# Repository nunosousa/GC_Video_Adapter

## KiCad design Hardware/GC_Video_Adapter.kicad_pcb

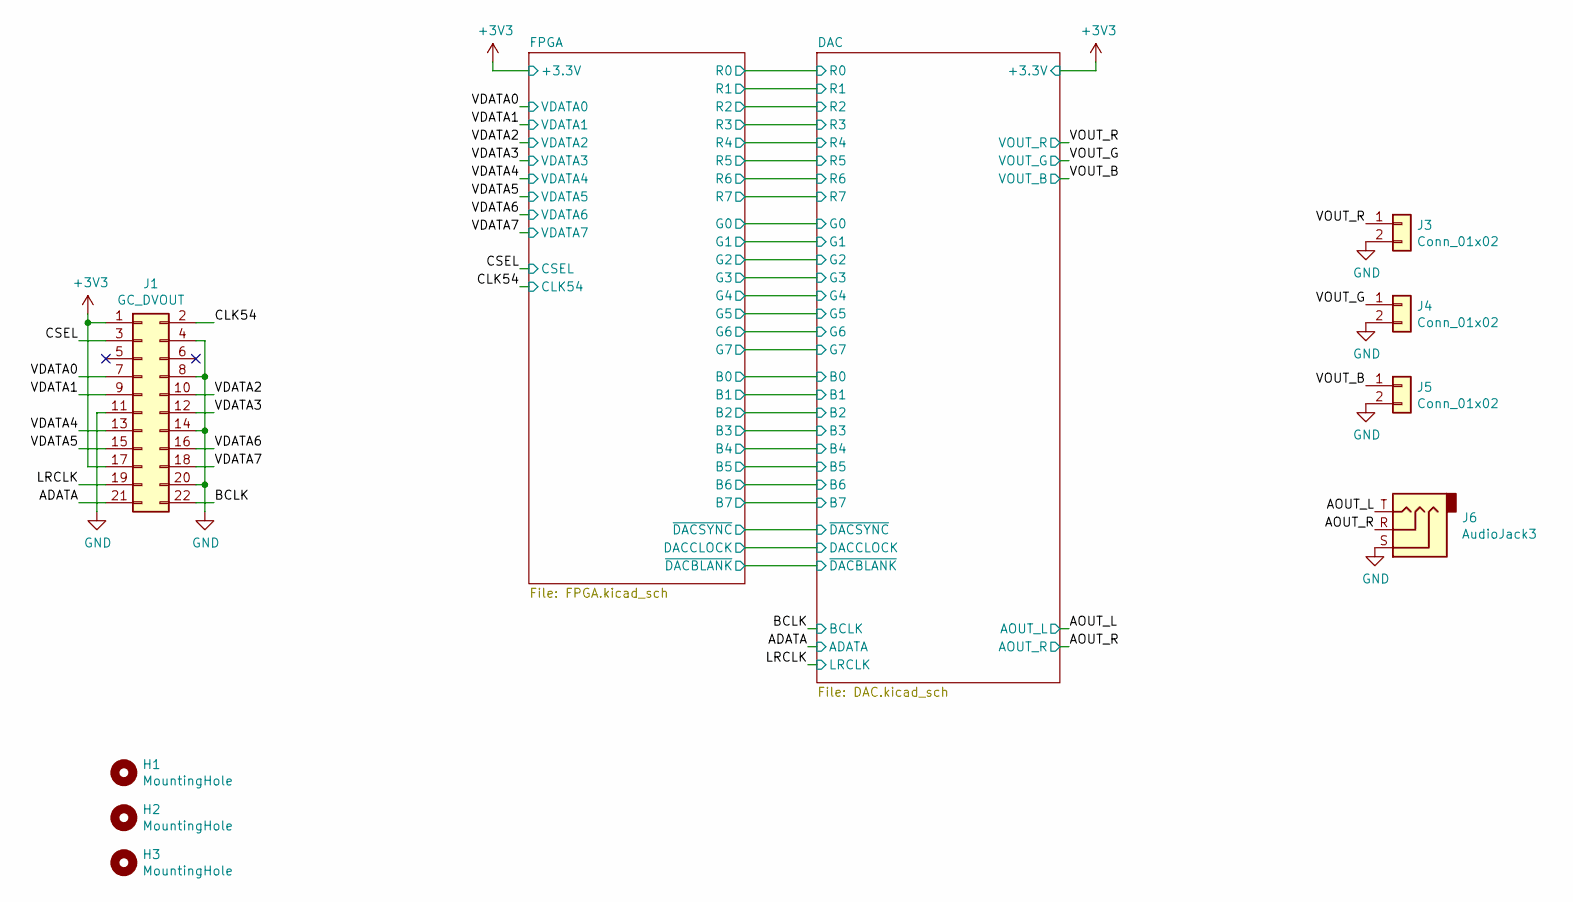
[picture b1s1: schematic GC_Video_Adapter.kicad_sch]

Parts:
H1, H2, H3: MountingHole; MountingHole_3.2mm_M3
J1: GC_DVOUT; GC-Connector-01; Manufacturer Part Number GC-Connector-01
J3, J4, J5: Conn_01x02; SolderWire-0.5sqmm_1x02_P4.6mm_D0.9mm_OD2.1mm
J6: AudioJack3; Jack_3.5mm_CUI_SJ1-3533NG_Horizontal; Manufacturer Part Number SJ1-3533NG

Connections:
+3V3: J1.1, J1.17; also elsewhere on the board
/ADATA: J1.21; also elsewhere on the board
/AOUT_L: J6.T; also elsewhere on the board
/AOUT_R: J6.R; also elsewhere on the board
/BCLK: J1.22; also elsewhere on the board
/CLK54: J1.2; also elsewhere on the board
/CSEL: J1.3; also elsewhere on the board
/LRCLK: J1.19; also elsewhere on the board
/VDATA0: J1.7; also elsewhere on the board
/VDATA1: J1.9; also elsewhere on the board
/VDATA2: J1.10; also elsewhere on the board
/VDATA3: J1.12; also elsewhere on the board
/VDATA4: J1.13; also elsewhere on the board
/VDATA5: J1.15; also elsewhere on the board
/VDATA6: J1.16; also elsewhere on the board
/VDATA7: J1.18; also elsewhere on the board
/VOUT_B: J5.1; also elsewhere on the board
/VOUT_G: J4.1; also elsewhere on the board
/VOUT_R: J3.1; also elsewhere on the board
GND: J1.4, J1.8, J1.11, J1.14, J1.20, J3.2, J4.2, J5.2, J6.S; also elsewhere on the board

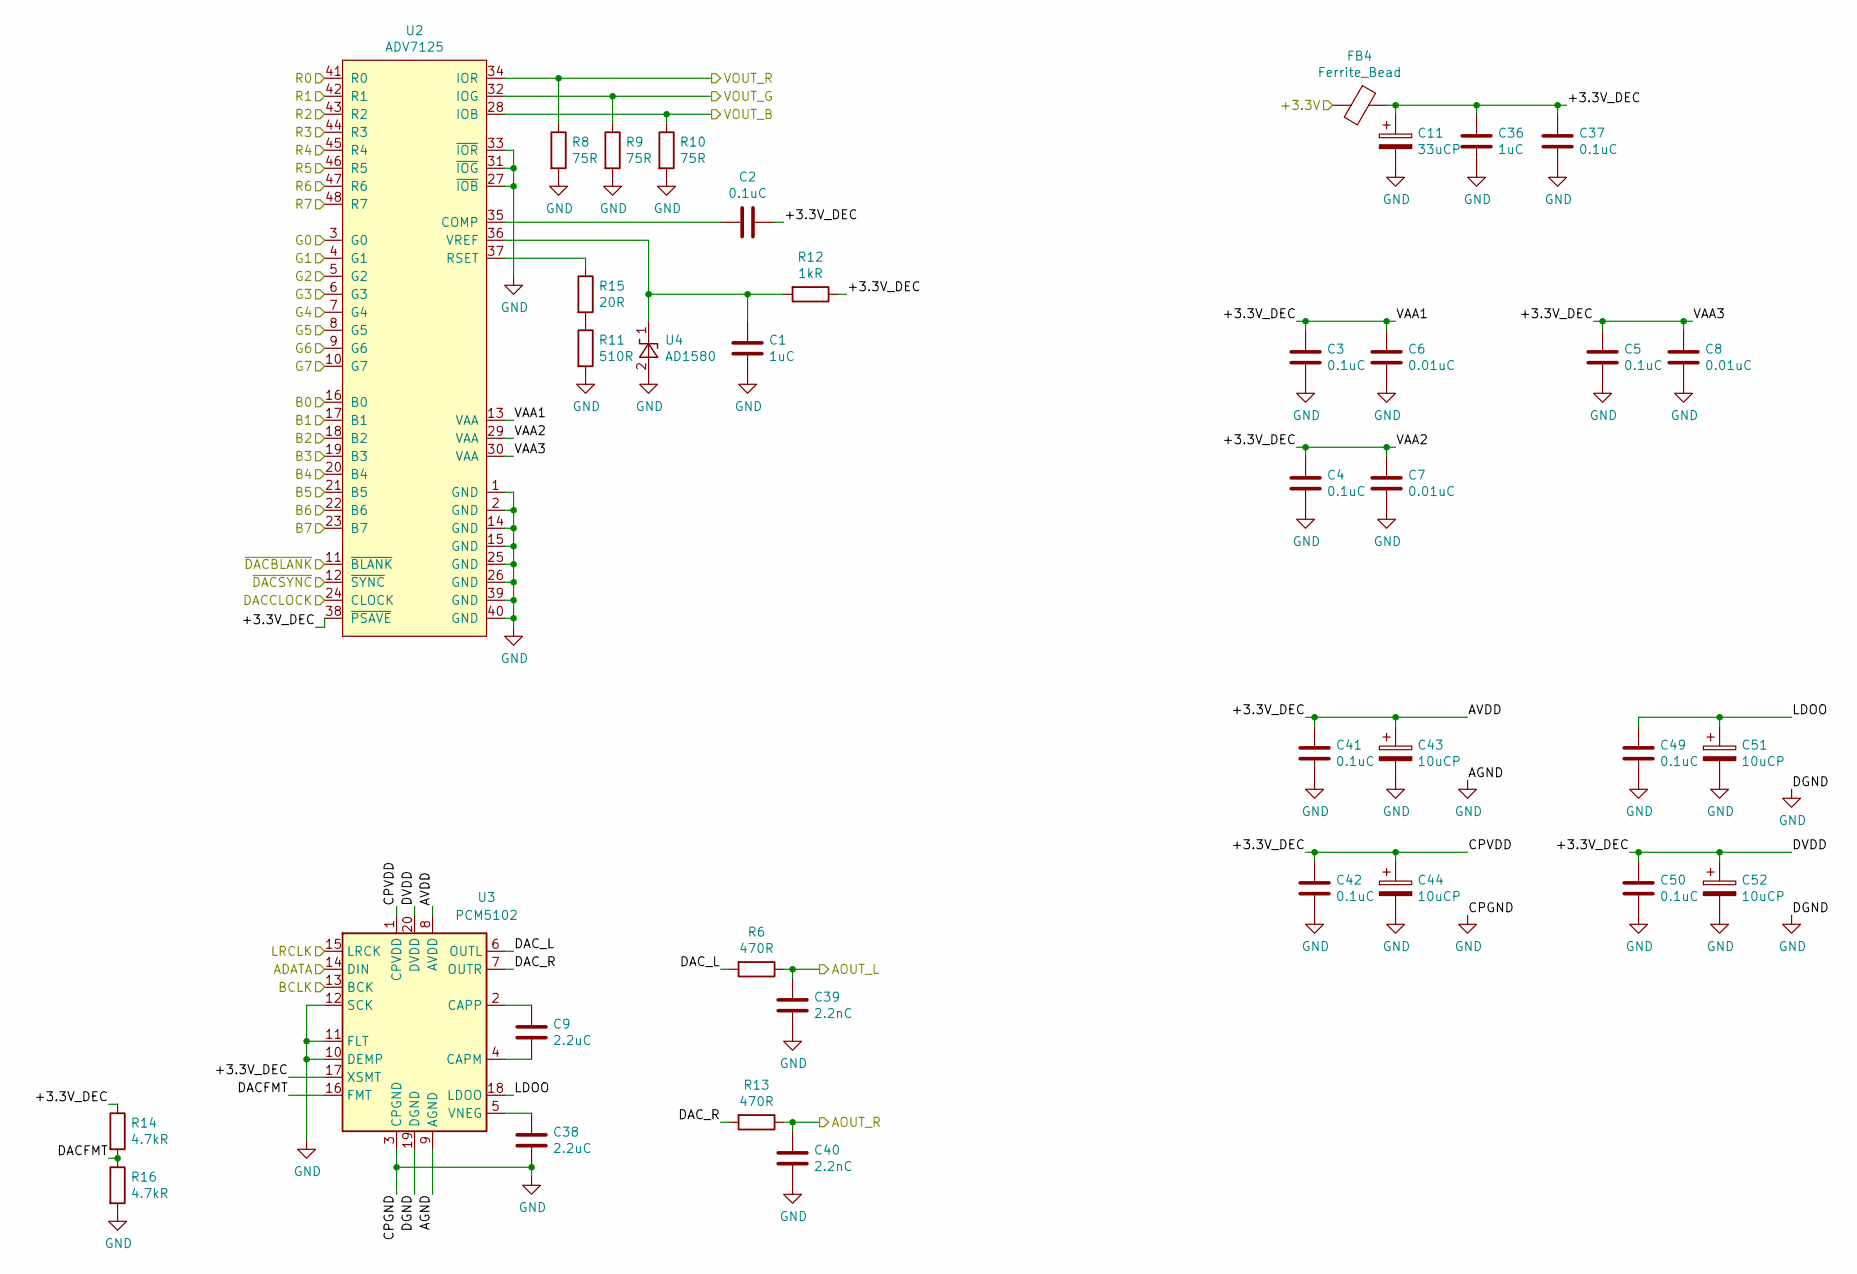
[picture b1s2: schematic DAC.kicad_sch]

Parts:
C1, C36: 1uC; C_0805_2012Metric_Pad1.18x1.45mm_HandSolder; Manufacturer Part Number CC0805MKX7R7BB105
C2, C3, C4, C5, C37, C41, C42, C49, C50: 0.1uC; C_0805_2012Metric_Pad1.18x1.45mm_HandSolder; Manufacturer Part Number AC0805KRX7R7BB104
C6, C7, C8: 0.01uC; C_0805_2012Metric_Pad1.18x1.45mm_HandSolder; Manufacturer Part Number CC0805KRX7R9BB103
C9, C38: 2.2uC; C_0805_2012Metric_Pad1.18x1.45mm_HandSolder; Manufacturer Part Number TMK212B7225KG-TR
C11: 33uCP; CP_EIA-3528-21_Kemet-B_Pad1.50x2.35mm_HandSolder; Manufacturer Part Number TAJB336K006RNJ
C39, C40: 2.2nC; C_0805_2012Metric_Pad1.18x1.45mm_HandSolder; Manufacturer Part Number FCP0805H222J-J1
C43, C44, C51, C52: 10uCP; CP_EIA-3216-18_Kemet-A_Pad1.58x1.35mm_HandSolder; Manufacturer Part Number TAJA106K006SNJ
FB4: Ferrite_Bead; L_0805_2012Metric_Pad1.15x1.40mm_HandSolder; Manufacturer Part Number BLM21SP471SH1D
R6, R13: 470R; R_0805_2012Metric_Pad1.20x1.40mm_HandSolder; Manufacturer Part Number CRCW0805470RJNEA
R8, R9, R10: 75R; R_0805_2012Metric_Pad1.20x1.40mm_HandSolder; Manufacturer Part Number RC0805FR-0775RL
R11: 510R; R_0805_2012Metric_Pad1.20x1.40mm_HandSolder; Manufacturer Part Number RT0805BRD07510RL
R12: 1kR; R_0805_2012Metric_Pad1.20x1.40mm_HandSolder; Manufacturer Part Number RC0805FR-071KL
R14, R16: 4.7kR; R_0805_2012Metric_Pad1.20x1.40mm_HandSolder; Manufacturer Part Number RC0805FR-074K7L
R15: 20R; R_0805_2012Metric_Pad1.20x1.40mm_HandSolder; Manufacturer Part Number RT0805BRD0720RL
U2: ADV7125; LQFP-48_7x7mm_P0.5mm; Manufacturer Part Number ADV7125KSTZ50-REEL
U3: PCM5102; TSSOP-20_4.4x6.5mm_P0.65mm; Manufacturer Part Number PCM5102APWR
U4: AD1580; SOT-23; Manufacturer Part Number AD1580BRTZ-REEL7

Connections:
+3V3: FB4.2; also elsewhere on the board
/ADATA: U3.14 (DIN); also elsewhere on the board
/AOUT_L: C39.1, R6.1; also elsewhere on the board
/AOUT_R: C40.1, R13.1; also elsewhere on the board
/BCLK: U3.13 (BCK); also elsewhere on the board
/DAC/+3.3V_DEC: C2.1, C3.1, C4.1, C5.1, C6.1, C7.1, C8.1, C11.1, C36.1, C37.1, C41.1, C42.1, C43.1, C44.1, C50.1, C52.1, FB4.1, R12.1, R14.1, U2.13 (VAA), U2.29 (VAA), U2.30 (VAA), U2.38 (~PSAVE), U3.1 (CPVDD), U3.8 (AVDD), U3.17 (XSMT), U3.20 (DVDD)
/DAC/B0: U2.16 (B0); also elsewhere on the board
/DAC/B1: U2.17 (B1); also elsewhere on the board
/DAC/B2: U2.18 (B2); also elsewhere on the board
/DAC/B3: U2.19 (B3); also elsewhere on the board
/DAC/B4: U2.20 (B4); also elsewhere on the board
/DAC/B5: U2.21 (B5); also elsewhere on the board
/DAC/B6: U2.22 (B6); also elsewhere on the board
/DAC/B7: U2.23 (B7); also elsewhere on the board
/DAC/DACCLOCK: U2.24 (CLOCK); also elsewhere on the board
/DAC/DACFMT: R14.2, R16.1, U3.16 (FMT)
/DAC/DAC_L: R6.2, U3.6 (OUTL)
/DAC/DAC_R: R13.2, U3.7 (OUTR)
/DAC/G0: U2.3 (G0); also elsewhere on the board
/DAC/G1: U2.4 (G1); also elsewhere on the board
/DAC/G2: U2.5 (G2); also elsewhere on the board
/DAC/G3: U2.6 (G3); also elsewhere on the board
/DAC/G4: U2.7 (G4); also elsewhere on the board
/DAC/G5: U2.8 (G5); also elsewhere on the board
/DAC/G6: U2.9 (G6); also elsewhere on the board
/DAC/G7: U2.10 (G7); also elsewhere on the board
/DAC/LDOO: C49.1, C51.1, U3.18 (LDOO)
/DAC/R0: U2.41 (R0); also elsewhere on the board
/DAC/R1: U2.42 (R1); also elsewhere on the board
/DAC/R2: U2.43 (R2); also elsewhere on the board
/DAC/R3: U2.44 (R3); also elsewhere on the board
/DAC/R4: U2.45 (R4); also elsewhere on the board
/DAC/R5: U2.46 (R5); also elsewhere on the board
/DAC/R6: U2.47 (R6); also elsewhere on the board
/DAC/R7: U2.48 (R7); also elsewhere on the board
/DAC/~DACBLANK: U2.11 (~BLANK); also elsewhere on the board
/DAC/~DACSYNC: U2.12 (~SYNC); also elsewhere on the board
/LRCLK: U3.15 (LRCK); also elsewhere on the board
/VOUT_B: R10.1, U2.28 (IOB); also elsewhere on the board
/VOUT_G: R9.1, U2.32 (IOG); also elsewhere on the board
/VOUT_R: R8.1, U2.34 (IOR); also elsewhere on the board
GND: C1.2, C3.2, C4.2, C5.2, C6.2, C7.2, C8.2, C11.2, C36.2, C37.2, C38.2, C39.2, C40.2, C41.2, C42.2, C43.2, C44.2, C49.2, C50.2, C51.2, C52.2, R8.2, R9.2, R10.2, R11.2, R16.2, U2.1 (GND), U2.2 (GND), U2.14 (GND), U2.15 (GND), U2.25 (GND), U2.26 (GND), U2.27 (~IOB), U2.31 (~IOG), U2.33 (~IOR), U2.39 (GND), U2.40 (GND), U3.3 (CPGND), U3.9 (AGND), U3.10 (DEMP), U3.11 (FLT), U3.12 (SCK), U3.19 (DGND), U4.2 (A); also elsewhere on the board
unnamed: C1.1, R12.2, U2.36 (VREF), U4.1 (K)
unnamed: C2.2, U2.35 (COMP)
unnamed: C9.1, U3.2 (CAPP)
unnamed: C9.2, U3.4 (CAPM)
unnamed: C38.1, U3.5 (VNEG)
unnamed: R11.1, R15.2
unnamed: R15.1, U2.37 (RSET)

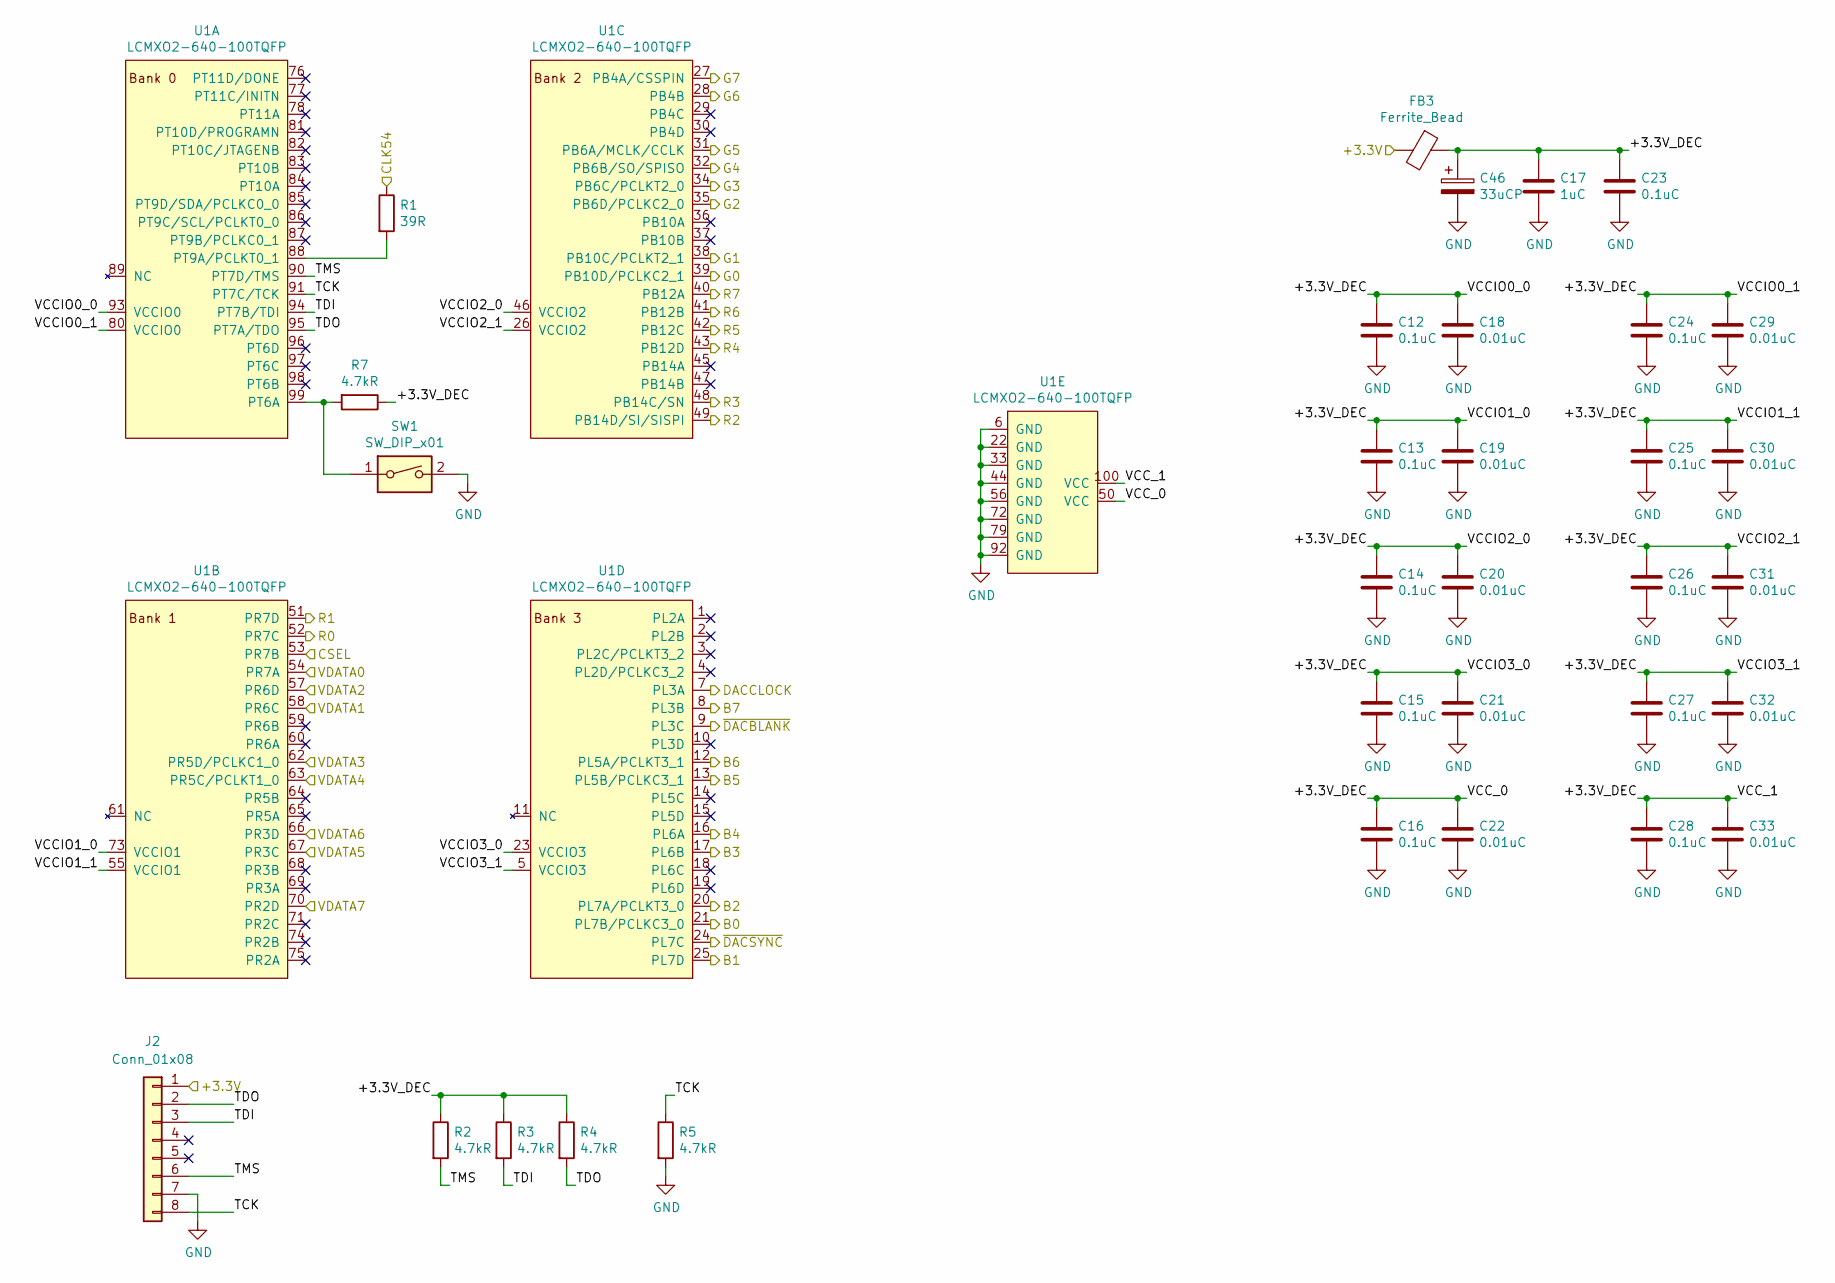
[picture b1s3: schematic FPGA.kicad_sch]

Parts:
C12, C13, C14, C15, C16, C23, C24, C25, C26, C27, C28: 0.1uC; C_0805_2012Metric_Pad1.18x1.45mm_HandSolder; Manufacturer Part Number AC0805KRX7R7BB104
C17: 1uC; C_0805_2012Metric_Pad1.18x1.45mm_HandSolder; Manufacturer Part Number CC0805MKX7R7BB105
C18, C19, C20, C21, C22, C29, C30, C31, C32, C33: 0.01uC; C_0805_2012Metric_Pad1.18x1.45mm_HandSolder; Manufacturer Part Number CC0805KRX7R9BB103
C46: 33uCP; CP_EIA-3528-21_Kemet-B_Pad1.50x2.35mm_HandSolder; Manufacturer Part Number TAJB336K006RNJ
FB3: Ferrite_Bead; L_0805_2012Metric_Pad1.15x1.40mm_HandSolder; Manufacturer Part Number BLM21SP471SH1D
J2: Conn_01x08; PinHeader_1x08_P2.54mm_Vertical; Manufacturer Part Number 0022284081
R1: 39R; R_0805_2012Metric_Pad1.20x1.40mm_HandSolder; Manufacturer Part Number RC0805FR-0739RL
R2, R3, R4, R5, R7: 4.7kR; R_0805_2012Metric_Pad1.20x1.40mm_HandSolder; Manufacturer Part Number RC0805FR-074K7L
SW1: SW_DIP_x01; SW_DIP_SPSTx01_Slide_6.7x4.1mm_W7.62mm_P2.54mm_LowProfile; Manufacturer Part Number DS04-254-2L-01BK
U1: LCMXO2-640-100TQFP; TQFP-100_14x14mm_P0.5mm; Manufacturer Part Number LCMXO2-640HC-4TG100I

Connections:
+3V3: FB3.2, J2.1; also elsewhere on the board
/CLK54: R1.1; also elsewhere on the board
/CSEL: U1.53 (PR7B); also elsewhere on the board
/DAC/B0: U1.21 (PL7B/PCLKC3_0); also elsewhere on the board
/DAC/B1: U1.25 (PL7D); also elsewhere on the board
/DAC/B2: U1.20 (PL7A/PCLKT3_0); also elsewhere on the board
/DAC/B3: U1.17 (PL6B); also elsewhere on the board
/DAC/B4: U1.16 (PL6A); also elsewhere on the board
/DAC/B5: U1.13 (PL5B/PCLKC3_1); also elsewhere on the board
/DAC/B6: U1.12 (PL5A/PCLKT3_1); also elsewhere on the board
/DAC/B7: U1.8 (PL3B); also elsewhere on the board
/DAC/DACCLOCK: U1.7 (PL3A); also elsewhere on the board
/DAC/G0: U1.39 (PB10D/PCLKC2_1); also elsewhere on the board
/DAC/G1: U1.38 (PB10C/PCLKT2_1); also elsewhere on the board
/DAC/G2: U1.35 (PB6D/PCLKC2_0); also elsewhere on the board
/DAC/G3: U1.34 (PB6C/PCLKT2_0); also elsewhere on the board
/DAC/G4: U1.32 (PB6B/SO/SPISO); also elsewhere on the board
/DAC/G5: U1.31 (PB6A/MCLK/CCLK); also elsewhere on the board
/DAC/G6: U1.28 (PB4B); also elsewhere on the board
/DAC/G7: U1.27 (PB4A/CSSPIN); also elsewhere on the board
/DAC/R0: U1.52 (PR7C); also elsewhere on the board
/DAC/R1: U1.51 (PR7D); also elsewhere on the board
/DAC/R2: U1.49 (PB14D/SI/SISPI); also elsewhere on the board
/DAC/R3: U1.48 (PB14C/SN); also elsewhere on the board
/DAC/R4: U1.43 (PB12D); also elsewhere on the board
/DAC/R5: U1.42 (PB12C); also elsewhere on the board
/DAC/R6: U1.41 (PB12B); also elsewhere on the board
/DAC/R7: U1.40 (PB12A); also elsewhere on the board
/DAC/~DACBLANK: U1.9 (PL3C); also elsewhere on the board
/DAC/~DACSYNC: U1.24 (PL7C); also elsewhere on the board
/FPGA/+3.3V_DEC: C12.1, C13.1, C14.1, C15.1, C16.1, C17.1, C18.1, C19.1, C20.1, C21.1, C22.1, C23.1, C24.1, C25.1, C26.1, C27.1, C28.1, C29.1, C30.1, C31.1, C32.1, C33.1, C46.1, FB3.1, R2.1, R3.1, R4.1, R7.1, U1.5 (VCCIO3), U1.23 (VCCIO3), U1.26 (VCCIO2), U1.46 (VCCIO2), U1.50 (VCC), U1.55 (VCCIO1), U1.73 (VCCIO1), U1.80 (VCCIO0), U1.93 (VCCIO0), U1.100 (VCC)
/FPGA/TCK: J2.8, R5.1, U1.91 (PT7C/TCK)
/FPGA/TDI: J2.3, R3.2, U1.94 (PT7B/TDI)
/FPGA/TDO: J2.2, R4.2, U1.95 (PT7A/TDO)
/FPGA/TMS: J2.6, R2.2, U1.90 (PT7D/TMS)
/VDATA0: U1.54 (PR7A); also elsewhere on the board
/VDATA1: U1.58 (PR6C); also elsewhere on the board
/VDATA2: U1.57 (PR6D); also elsewhere on the board
/VDATA3: U1.62 (PR5D/PCLKC1_0); also elsewhere on the board
/VDATA4: U1.63 (PR5C/PCLKT1_0); also elsewhere on the board
/VDATA5: U1.67 (PR3C); also elsewhere on the board
/VDATA6: U1.66 (PR3D); also elsewhere on the board
/VDATA7: U1.70 (PR2D); also elsewhere on the board
GND: C12.2, C13.2, C14.2, C15.2, C16.2, C17.2, C18.2, C19.2, C20.2, C21.2, C22.2, C23.2, C24.2, C25.2, C26.2, C27.2, C28.2, C29.2, C30.2, C31.2, C32.2, C33.2, C46.2, J2.7, R5.2, SW1.2, U1.6 (GND), U1.22 (GND), U1.33 (GND), U1.44 (GND), U1.56 (GND), U1.72 (GND), U1.79 (GND), U1.92 (GND); also elsewhere on the board
unnamed: R1.2, U1.88 (PT9A/PCLKT0_1)
unnamed: R7.2, SW1.1, U1.99 (PT6A)

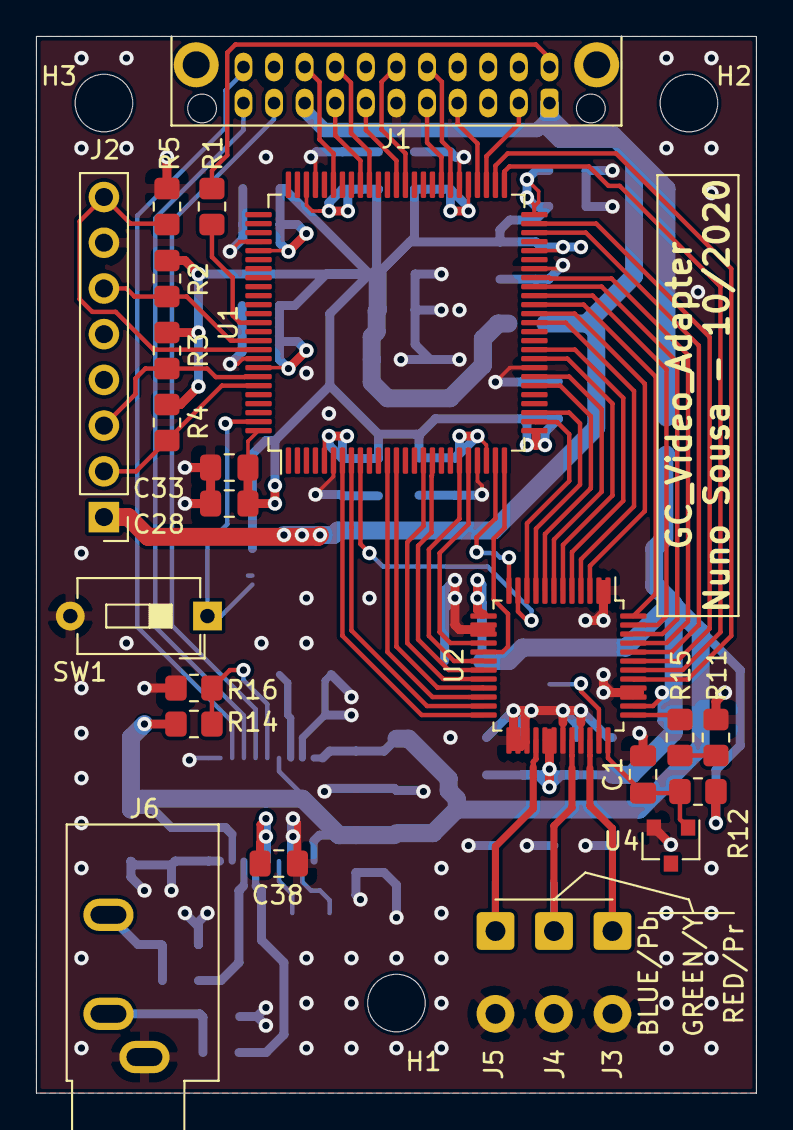
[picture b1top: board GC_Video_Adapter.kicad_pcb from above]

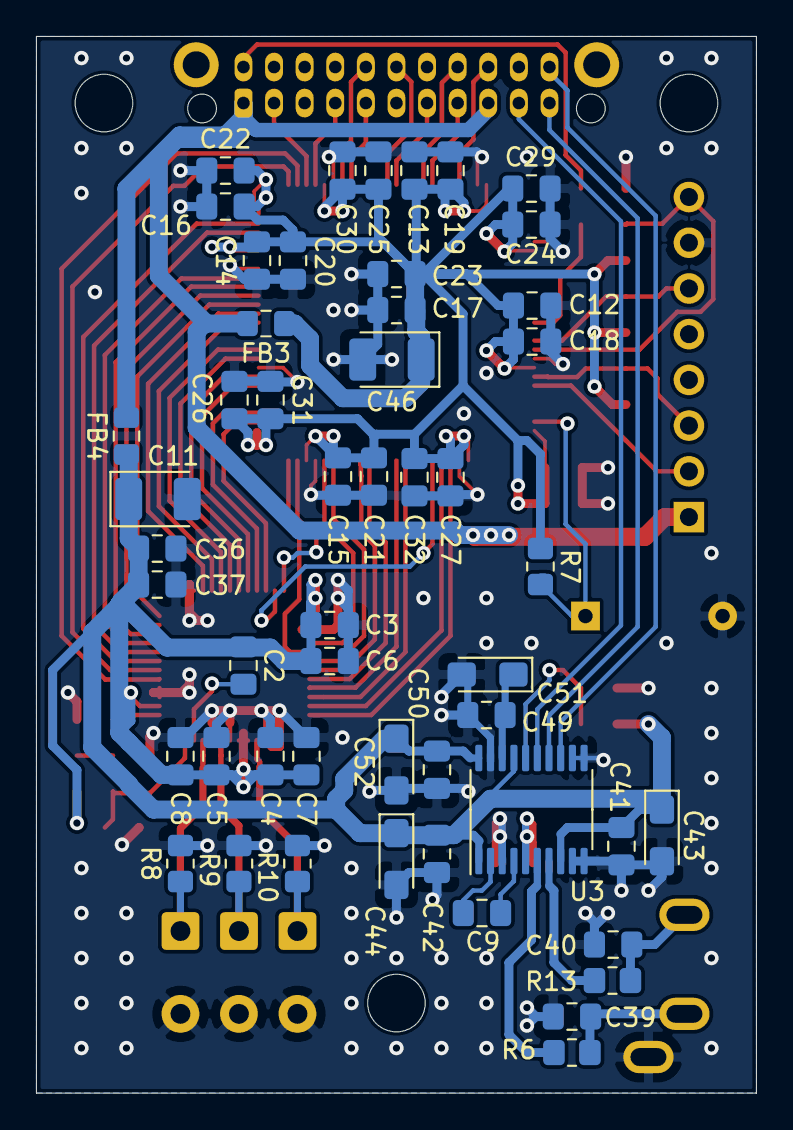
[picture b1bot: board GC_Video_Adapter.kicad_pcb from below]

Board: 4 copper layers, 40.0 x 58.7 mm, 78 parts (51 on the bottom side), 66 nets.

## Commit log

2020-12-12 Created HDL project.
2020-12-30 Changed file type do vhdl.
2020-12-31 Project update.
2021-01-01 Source update.
2021-01-02 Update source code.
2021-01-02 gc_dv_decode.vhd ready for test bench
2021-01-04 Created test bench file.
2021-01-04 TB update
2021-01-05 Progressed test bench.
2021-01-14 Progressed logic analisys.
2021-01-14 Added skeletong for the YCrCb to RGB.
2021-01-19 Added top level file.
2021-02-09 Progressed updates.
2021-02-09 Progressed work.
2021-02-14 Removed reset
2021-02-14 Tidy up.
2021-02-23 Rename gc_dv_decode_tb.vhd to gc_dv_decode_tb01.vhd
2021-02-23 Rename gc_dv_422_to_444_tb.vhd to gc_dv_422_to_444_tb01.vhd
2021-02-23 Rename gc_dv_top_level_tb.vhd to gc_dv_top_level_tb01.vhd
2021-02-27 Updated simulation results
2021-02-27 added ghdl commands
2021-02-27 Updated upsampling logic.
2021-02-28 Update.
2021-02-28 Updated RGB convergion skeleton.
2021-02-28 Updated toplevel.
2021-02-28 updated notes
2021-02-28 Minor fixes.
2021-02-28 Added new test and results.
2021-02-28 Added more test benches.
2021-03-01 Updated test.
2021-03-01 Fixed bug on upsampling logic.
2021-03-02 Progressed design.
2021-03-03 Updated file tree
2021-03-03 Progressed makefile
2021-03-03 Minor update.
2021-03-04 Created Lattice Diamond project.
2021-03-05 Minor project updates.
2021-03-06 Removed initial values.
2021-03-06 updated simulation files
2021-03-06 Rerun of testbenches.
2021-03-06 Clean up.
2021-03-07 minor update
2021-03-08 Replaced variables with signals to improve timing.
2021-03-08 Refactored pixel clock logic.
2021-03-08 Refactored decode logic.
2021-03-09 Alternative to existing logic.
2021-03-10 State machine split.
2021-03-10 pclk
2021-03-11 Updated decode logic.
2021-03-11 Progressed logic updates.
2021-03-12 Progressed logic changes.
2021-03-12 Progressed logic.
2021-03-12 Progressed logic update.
2021-03-13 Solved compiling errors.
2021-03-13 Progressed logic update
2021-03-14 Updated logic.
2021-03-14 Typo fix.
2021-03-14 Updated simulation results.
2021-03-14 Revert "Update GC_Video_Adapter.ldf"
    This reverts commit 2a1de125aa7ca14c4b4dcd3b71345d6bd1fdcc42.
2021-03-14 Revert "Revert "Update GC_Video_Adapter.ldf""
    This reverts commit a778dbec3f41ac53dd80529b6ccdd5e9b3f460e7.
2024-04-14 Upgraded from Kicad 5 to Kicad 8.
